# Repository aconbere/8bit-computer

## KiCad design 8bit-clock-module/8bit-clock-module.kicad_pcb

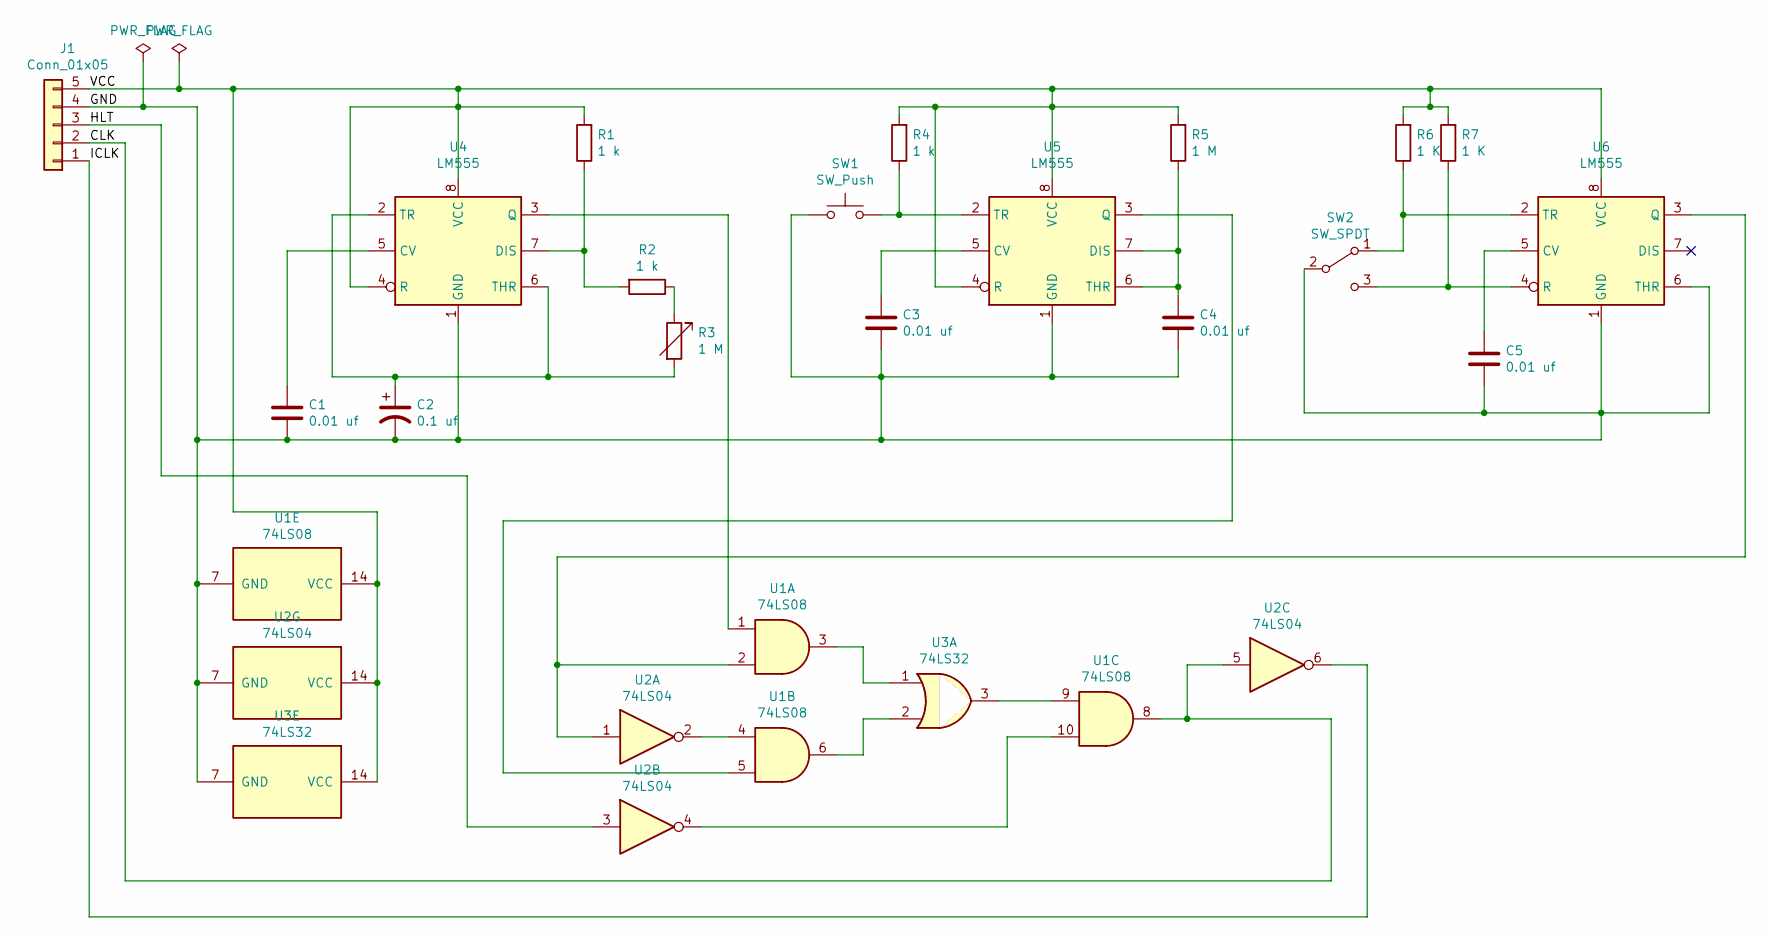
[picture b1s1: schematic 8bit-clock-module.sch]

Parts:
C1, C3, C4, C5: 0.01 uf; C_Disc_D5.1mm_W3.2mm_P5.00mm
C2: 0.1 uf; C_Disc_D5.1mm_W3.2mm_P5.00mm
J1: Conn_01x05; JST_EH_B05B-EH-A_1x05_P2.50mm_Vertical
R1: 1 k; R_Axial_DIN0204_L3.6mm_D1.6mm_P5.08mm_Horizontal
R2, R4: 1 k; R_Axial_DIN0204_L3.6mm_D1.6mm_P5.08mm_Vertical
R3, R5: 1 M; R_Axial_DIN0204_L3.6mm_D1.6mm_P5.08mm_Vertical
R6, R7: 1 K; R_Axial_DIN0204_L3.6mm_D1.6mm_P5.08mm_Vertical
SW1: SW_Push; SW_PUSH_6mm
SW2: SW_SPDT; SW_SPDT_CK-JS102011SAQN
U1: 74LS08; DIP-14_W7.62mm
U2: 74LS04; DIP-14_W7.62mm
U3: 74LS32; DIP-14_W7.62mm
U4, U5, U6: LM555; DIP-8_W7.62mm

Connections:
/CLK: J1.2, U1.8, U2.5
/GND: C1.2, C2.2, C3.2, C4.2, C5.2, J1.4, SW1.1, SW2.2 (B), U1.7 (GND), U2.7 (GND), U3.7 (GND), U4.1 (GND), U5.1 (GND), U6.1 (GND), U6.6 (THR)
/HLT: J1.3, U2.3
/ICLK: J1.1, U2.6
/VCC: J1.5, R1.2, R4.2, R5.2, R6.2, R7.2, U1.14 (VCC), U2.14 (VCC), U3.14 (VCC), U4.4 (R), U4.8 (VCC), U5.4 (R), U5.8 (VCC), U6.8 (VCC)
unnamed: C1.1, U4.5 (CV)
unnamed: C2.1, R3.2, U4.2 (TR), U4.6 (THR)
unnamed: C3.1, U5.5 (CV)
unnamed: C4.1, R5.1, U5.6 (THR), U5.7 (DIS)
unnamed: C5.1, U6.5 (CV)
unnamed: R1.1, R2.2, U4.7 (DIS)
unnamed: R2.1, R3.1
unnamed: R4.1, SW1.2, U5.2 (TR)
unnamed: R6.1, SW2.1 (A), U6.2 (TR)
unnamed: R7.1, SW2.3 (C), U6.4 (R)
unnamed: U1.1, U4.3 (Q)
unnamed: U1.2, U2.1, U6.3 (Q)
unnamed: U1.3, U3.1
unnamed: U1.4, U2.2
unnamed: U1.5, U5.3 (Q)
unnamed: U1.6, U3.2
unnamed: U1.9, U3.3
unnamed: U1.10, U2.4

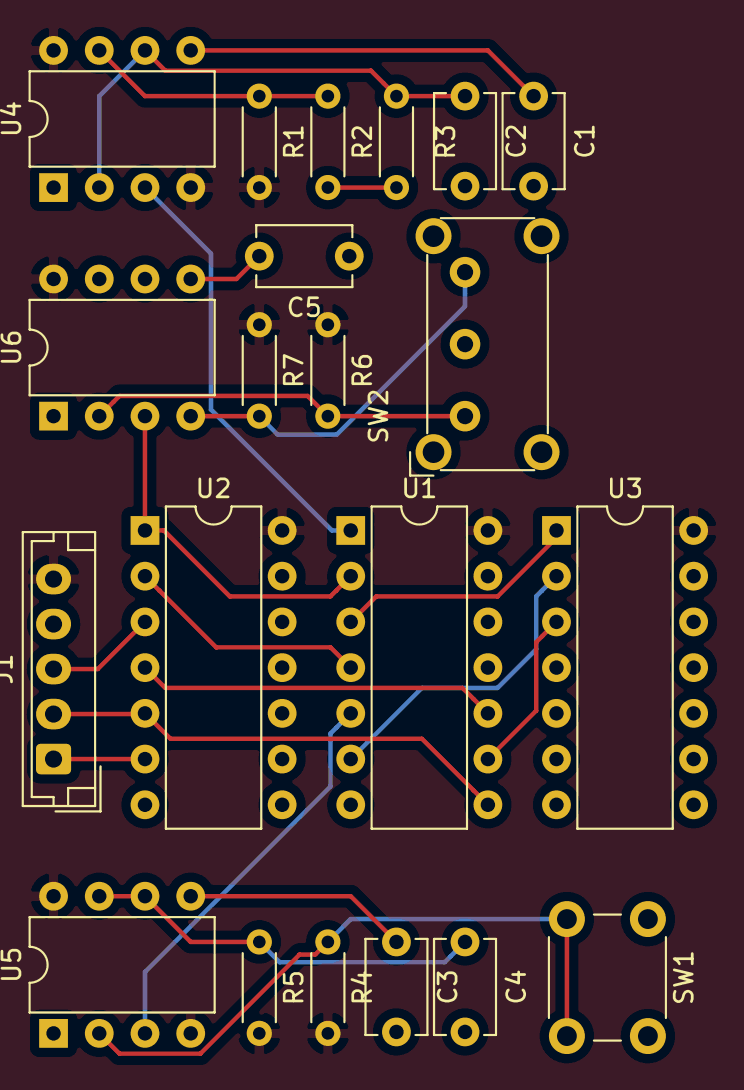
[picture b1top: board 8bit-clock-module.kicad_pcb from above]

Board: 2 copper layers, 21 parts (0 on the bottom side), 23 nets.

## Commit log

2020-04-10 First commit of clock module pcb + eeprom programmer
2020-05-15 Got no unconnected pins
